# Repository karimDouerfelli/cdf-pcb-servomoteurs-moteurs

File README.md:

# 🛠️ PCB Servomoteurs & Moteurs – Coupe de France de Robotique 2026

Ce projet est un PCB dédié au pilotage de **moteurs** et **servomoteurs**, conçu pour la **Coupe de France de Robotique 2026**.

## ⚙️ Fonctionnalités principales

- Contrôle de servomoteurs via :
  - **UART**
  - **PWM**
- Carte en **4 couches** avec une **couche Power** divisée en 3 zones.

---

## 🧩 Schéma

### Schéma global :

### STM32 et ses compléments :

### Régulateurs :

---

## 🧱 Empreintes

---

## 🧵 Routage

### Placement des composants :

---

## 🧭 Couches PCB

- **GND Layer** :  

- **Top Layer (Rouge)** :  

- **Bottom Layer (Bleue)** :  

- **Power Layer** :  

---

## 📏 Dimensionnement des pistes

Nous avons utilisé la formule suivante pour calculer la largeur des pistes selon le courant attendu :

---

## 🙏 Remerciements

Merci à **@CaptainJaja** pour son aide sur le projet ❤️  

---

## 💬 Retours bienvenus

N'hésitez pas à **ouvrir une issue** ou **créer une pull request** si vous avez des remarques ou des suggestions.

---

---

# 🛠️ PCB for Servomotors & Motors – French Robotics Cup 2026

This project is a PCB designed to control **motors** and especially **servomotors**, built for the **French Robotics Cup 2026**.

## ⚙️ Key Features

- Supports two control modes for servos:
  - **UART**
  - **PWM**
- Built on a **4-layer board** with a **Power layer** split into 3 zones.

---

## 🧩 Schematics

### Global schematic:

### STM32 and peripherals:

### Voltage regulators:

---

## 🧱 Footprints

---

## 🧵 Routing

### Component placement:

---

## 🧭 PCB Layers

- **GND Layer**  

- **Top Layer (Red)**  

- **Bottom Layer (Blue)**  

- **Power Layer**  

---

## 📏 Trace Sizing

Trace widths were calculated using the following formula based on expected current:

---

## 🙏 Acknowledgments

Big thanks to **@CaptainJaja** for contributions ❤️  

---

## 💬 Feedback

Feel free to **open an issue** or **submit a pull request** if you have ideas or improvements to suggest.

---

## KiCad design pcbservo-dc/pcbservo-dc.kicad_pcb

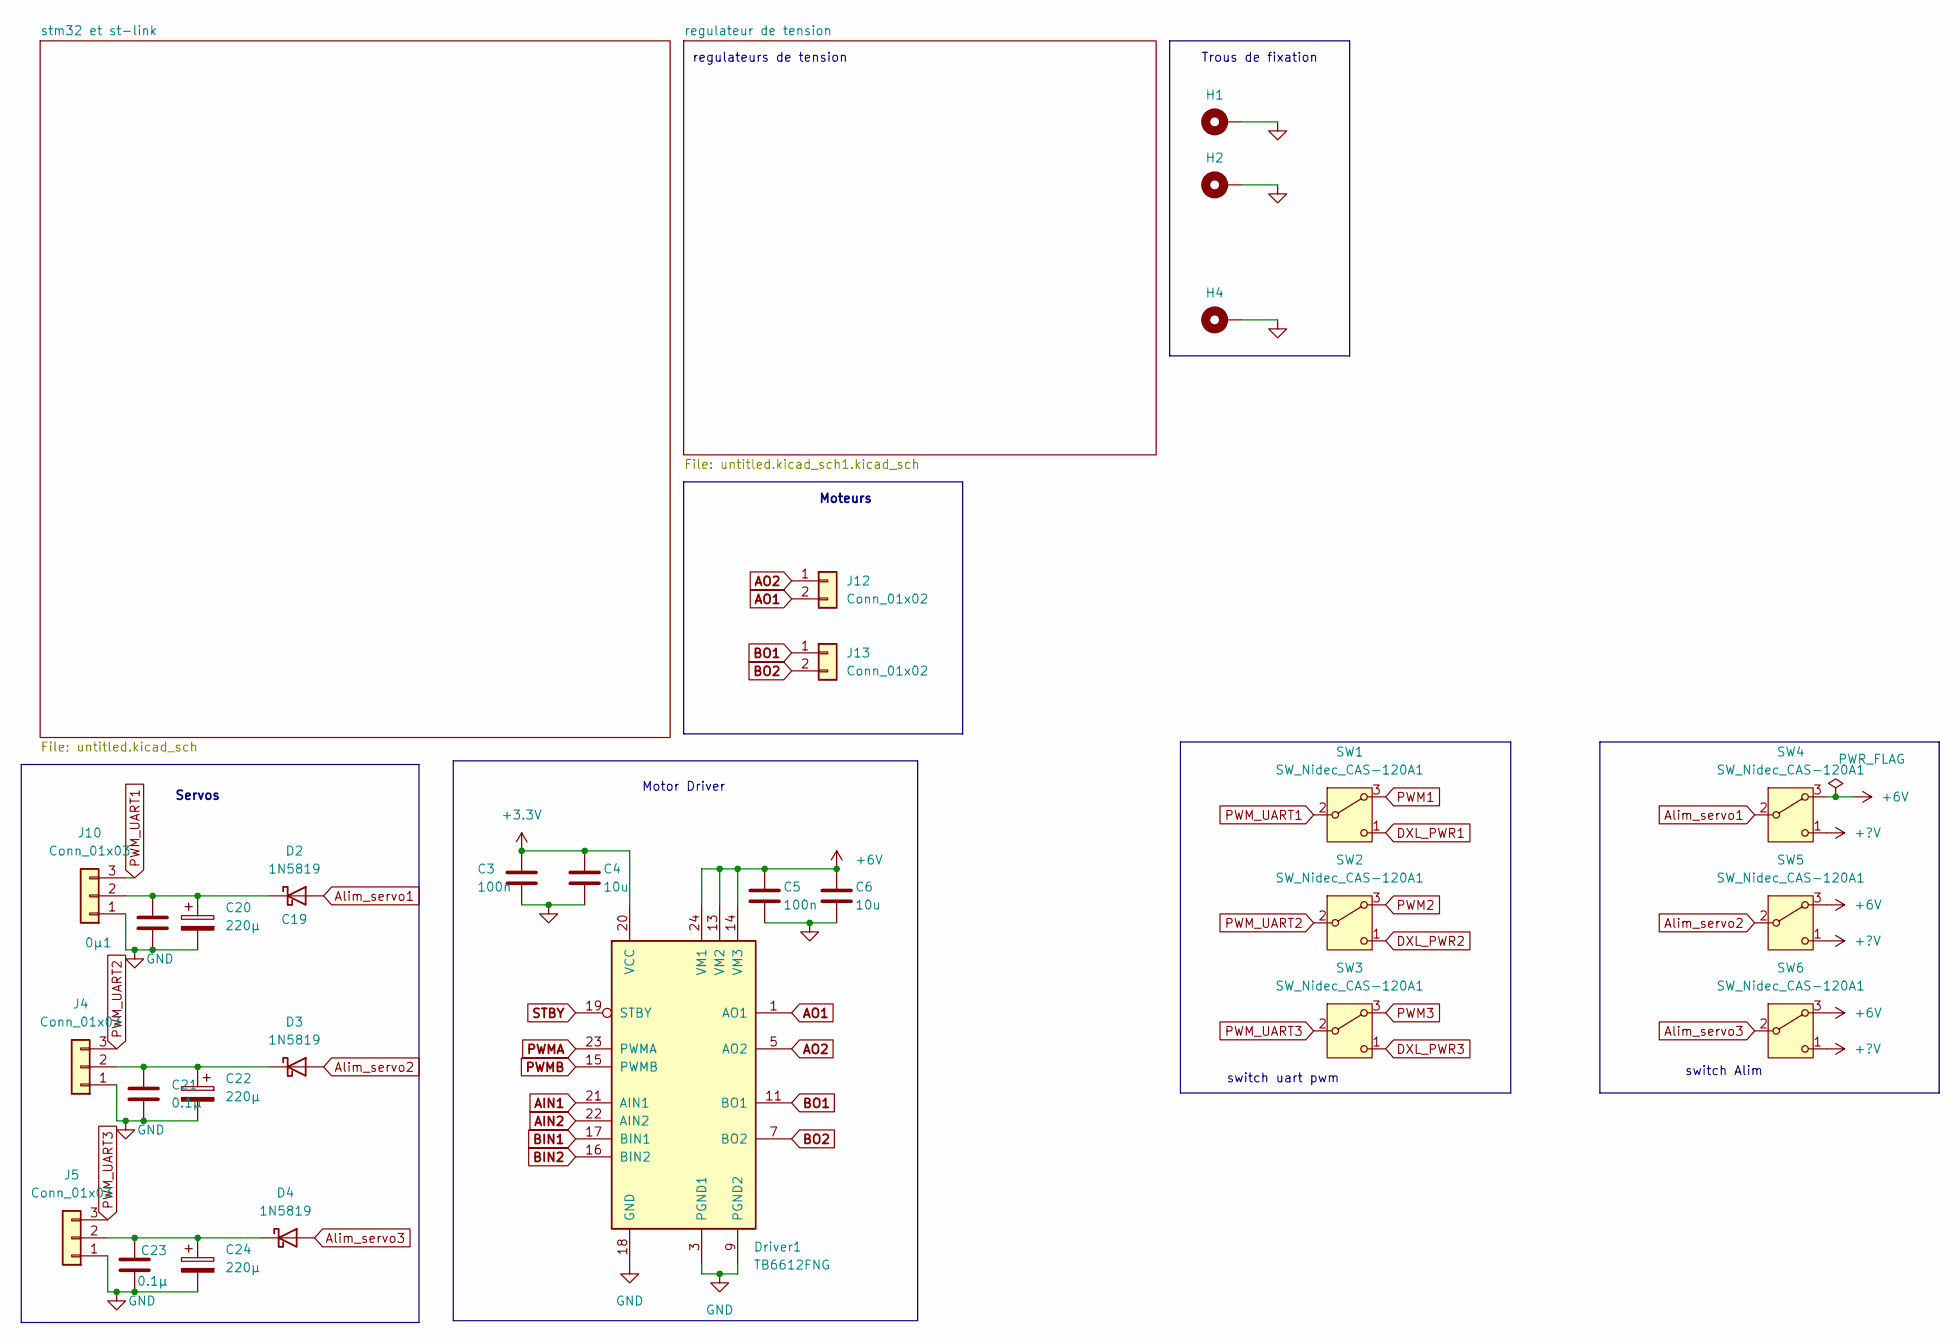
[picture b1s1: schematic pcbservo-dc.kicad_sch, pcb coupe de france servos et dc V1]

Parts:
C3, C5: 100n; C_0402_1005Metric
C4, C6: 10u; C_0805_2012Metric
C19: 0µ1; C_0805_2012Metric
C20, C22, C24: 220µ; CAPPRD500W60D1000H2500
C21, C23: 0.1µ; C_0805_2012Metric
D2, D3, D4: 1N5819; D_SOD-123
Driver1: TB6612FNG; SSOP-24_5.3x8.2mm_P0.65mm
H1, H2, H4: MountingHole_Pad; MountingHole_2.7mm_M2.5_Pad
J4, J5, J10: Conn_01x03; JST_EH_B3B-EH-A_1x03_P2.50mm_Vertical
J12, J13: Conn_01x02; JST_EH_B2B-EH-A_1x02_P2.50mm_Vertical
SW1, SW2, SW3, SW4, SW5, SW6: SW_Nidec_CAS-120A1; Nidec_Copal_CAS-120A

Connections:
+3.3V: C3.1, C4.1, Driver1.20 (VCC); also elsewhere on the board
+6V: C5.1, C6.1, Driver1.13 (VM2), Driver1.14 (VM3), Driver1.24 (VM1), SW4.3 (A), SW5.3 (A), SW6.3 (A); also elsewhere on the board
+?V: SW4.1 (C), SW5.1 (C), SW6.1 (C); also elsewhere on the board
AIN1: Driver1.21 (AIN1); also elsewhere on the board
AIN2: Driver1.22 (AIN2); also elsewhere on the board
AO1: Driver1.1 (AO1), Driver1.2 (AO1), J12.2
AO2: Driver1.5 (AO2), Driver1.6 (AO2), J12.1
Alim_servo1: D2.2 (A), SW4.2 (B)
Alim_servo2: D3.2 (A), SW5.2 (B)
Alim_servo3: D4.2 (A), SW6.2 (B)
BIN1: Driver1.17 (BIN1); also elsewhere on the board
BIN2: Driver1.16 (BIN2); also elsewhere on the board
BO1: Driver1.11 (BO1), Driver1.12 (BO1), J13.1
BO2: Driver1.7 (BO2), Driver1.8 (BO2), J13.2
DXL_PWR1: SW1.1 (C); also elsewhere on the board
DXL_PWR2: SW2.1 (C); also elsewhere on the board
DXL_PWR3: SW3.1 (C); also elsewhere on the board
GND: C3.2, C4.2, C5.2, C6.2, C19.2, C20.2, C21.2, C22.2, C23.2, C24.2, Driver1.3 (PGND1), Driver1.4 (PGND1), Driver1.9 (PGND2), Driver1.10 (PGND2), Driver1.18 (GND), H1.1, H2.1, H4.1, J4.1, J5.1, J10.1; also elsewhere on the board
unnamed: C19.1, C20.1, D2.1 (K), J10.2
unnamed: C21.1, C22.1, D3.1 (K), J4.2
unnamed: C23.1, C24.1, D4.1 (K), J5.2
PWM1: SW1.3 (A); also elsewhere on the board
PWM2: SW2.3 (A); also elsewhere on the board
PWM3: SW3.3 (A); also elsewhere on the board
PWMA: Driver1.23 (PWMA); also elsewhere on the board
PWMB: Driver1.15 (PWMB); also elsewhere on the board
PWM_UART1: J10.3, SW1.2 (B)
PWM_UART2: J4.3, SW2.2 (B)
PWM_UART3: J5.3, SW3.2 (B)
STBY: Driver1.19 (STBY); also elsewhere on the board

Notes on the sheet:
Trous de fixation
switch uart pwm
Servos
switch Alim
regulateurs de tension
Moteurs
Motor Driver

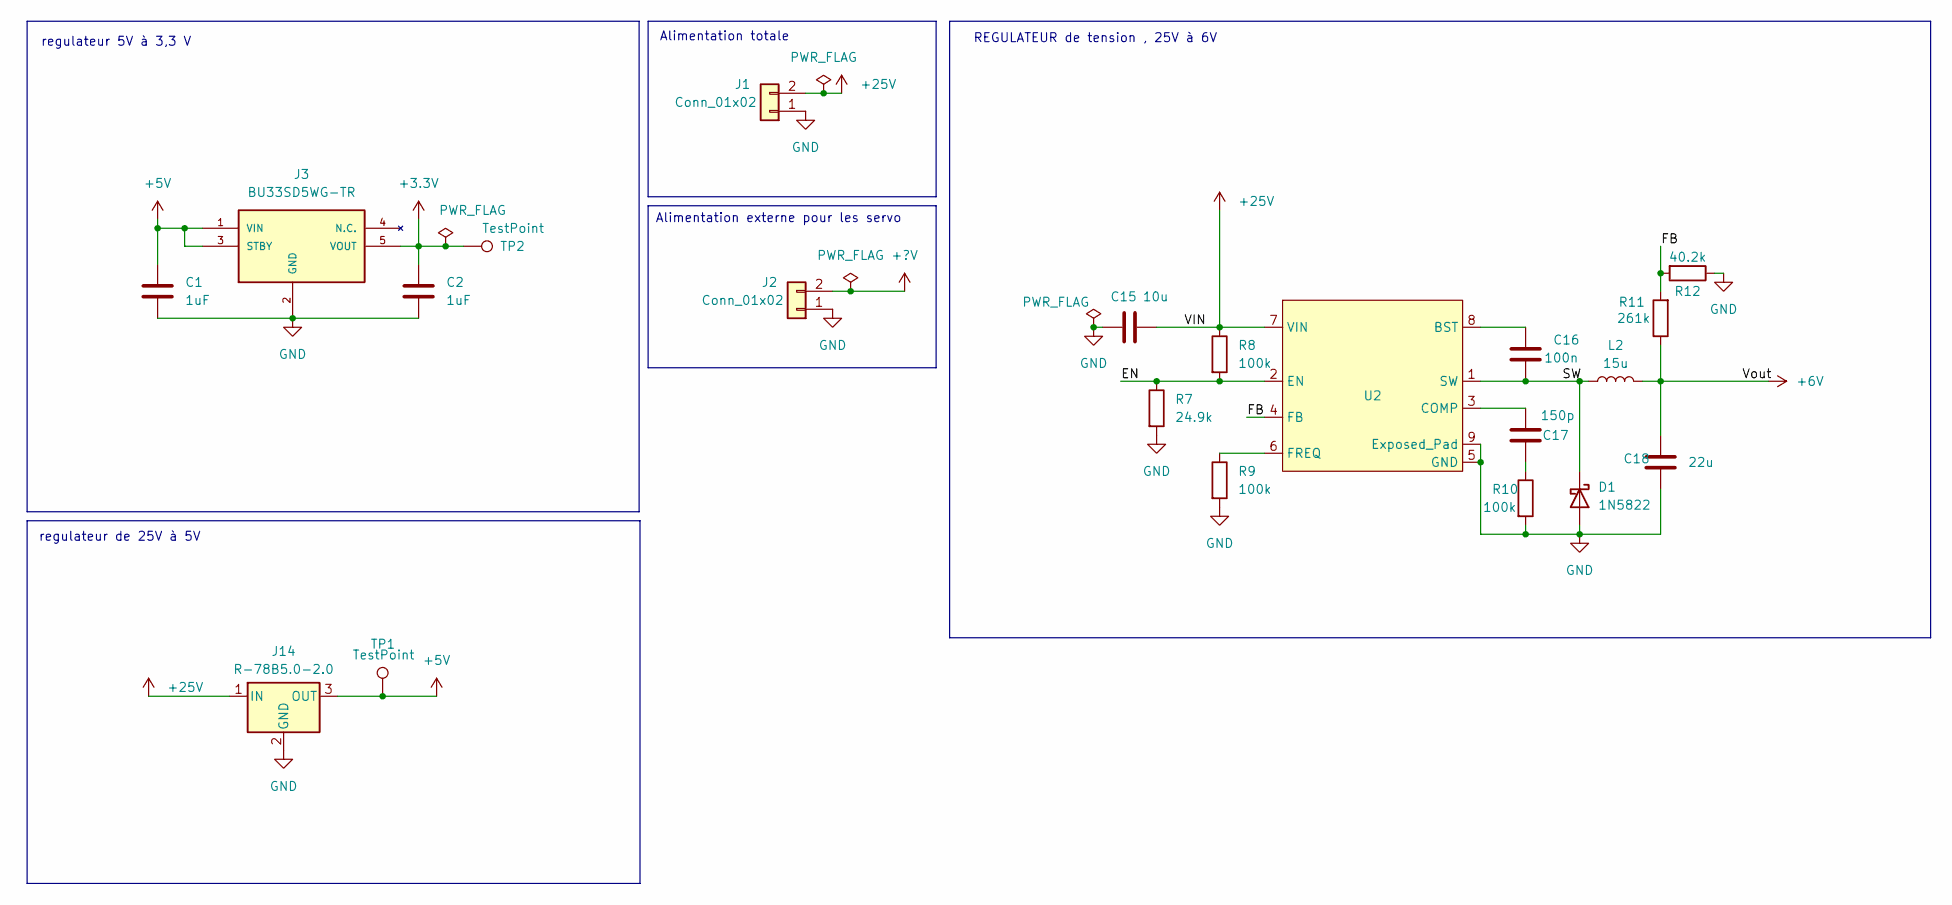
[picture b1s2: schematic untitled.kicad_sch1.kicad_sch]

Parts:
C1, C2: 1uF; C_0603_1608Metric_Pad1.08x0.95mm_HandSolder
C15: 10u; C_0603_1608Metric
C16: 100n; C_0603_1608Metric
C17: 150p; C_0603_1608Metric
C18: 22u; C_0805_2012Metric
D1: 1N5822; D_SMB
J1, J2: Conn_01x02; JST_EH_B2B-EH-A_1x02_P2.50mm_Vertical
J3: BU33SD5WG-TR; SOT-23-5; Mouser_Part_Number 755-BU33SD5WG-TR
J14: R-78B5.0-2.0; Converter_DCDC_RECOM_R-78B-2.0_THT
L2: 15u; L_12x12mm_H4.5mm
R7: 24.9k; R_0603_1608Metric
R8, R9, R10: 100k; R_0603_1608Metric
R11: 261k; R_0603_1608Metric
R12: 40.2k; R_0603_1608Metric
TP1, TP2: TestPoint; TestPoint_Pad_D1.0mm
U2: MP1584-SOICP8

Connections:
+3.3V: C2.1, J3.5 (VOUT), TP2.1; also elsewhere on the board
+5V: C1.1, J3.1 (VIN), J3.3 (STBY), J14.3 (OUT), TP1.1; also elsewhere on the board
+6V: C18.1, L2.2, R11.1; also elsewhere on the board
+25V: C15.1, J1.2, J14.1 (IN), R8.1, U2.7 (VIN)
+?V: J2.2; also elsewhere on the board
/regulateur de tension/EN: R7.1, R8.2, U2.2 (EN)
/regulateur de tension/FB: R11.2, R12.2, U2.4 (FB)
/regulateur de tension/SW: C16.2, D1.1 (K), L2.1, U2.1 (SW)
GND: C1.2, C2.2, C15.2, C18.2, D1.2 (A), J1.1, J2.1, J3.2 (GND), J14.2 (GND), R7.2, R9.2, R10.2, R12.1, U2.5 (GND), U2.9 (Exposed_Pad); also elsewhere on the board
unnamed: C17.2, R10.1
unnamed: C16.1, U2.8 (BST)
unnamed: C17.1, U2.3 (COMP)
unnamed: R9.1, U2.6 (FREQ)

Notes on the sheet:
regulateur 5V à 3,3 V
Alimentation externe pour les servo
REGULATEUR de tension , 25V à 6V
regulateur de 25V à 5V
Alimentation totale

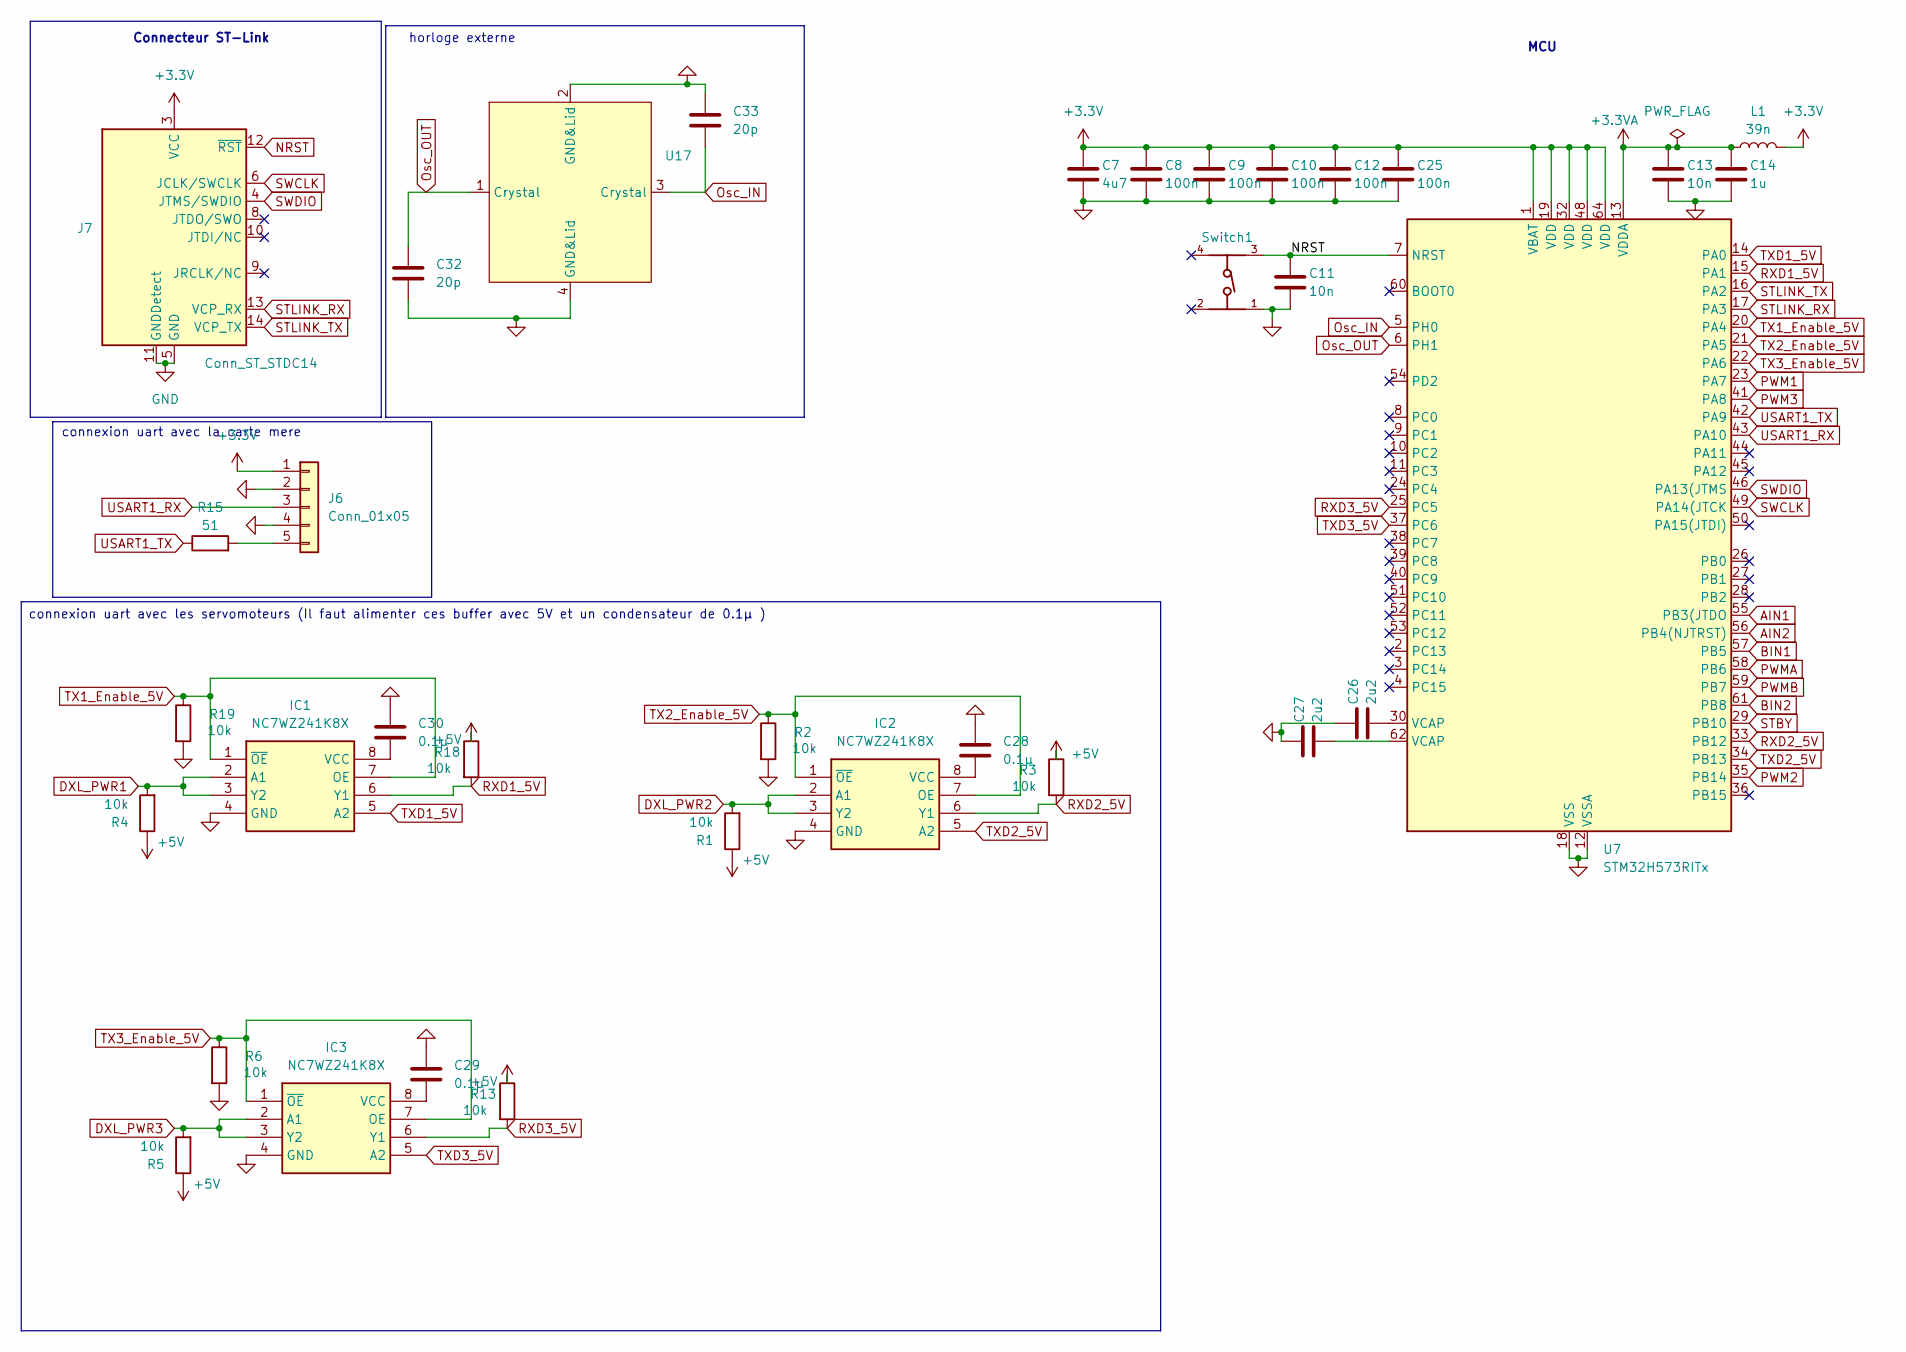
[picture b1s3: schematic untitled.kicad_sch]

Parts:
C7: 4u7; C_0805_2012Metric
C8, C9, C10, C12, C25: 100n; C_0402_1005Metric
C11, C13: 10n; C_0402_1005Metric
C14: 1u; C_0402_1005Metric
C26, C27: 2u2; C_0805_2012Metric
C28, C29, C30: 0.1µ; C_0603_1608Metric
C32, C33: 20p; C_0603_1608Metric
IC1, IC2, IC3: NC7WZ241K8X; UQFN8 1.6X1.6, 0.5P; Mouser Part Number 512-NC7WZ241K8X
J6: Conn_01x05; JST_EH_B5B-EH-A_1x05_P2.50mm_Vertical
J7: Conn_ST_STDC14; PinHeader_2x07_P1.27mm_Vertical_SMD
L1: 39n; L_0603_1608Metric
R1, R2, R3, R4, R5, R6, R13, R18, R19: 10k; R_0402_1005Metric
R15: 51; R_0402_1005Metric
Switch1: 430471025826; BOUTONPOUSSOIR; PART-NUMBER 430471025826
U7: STM32H573RITx; LQFP-64_10x10mm_P0.5mm
U17: Crystal_SMD_3225-4Pin_3.2x2.5mm

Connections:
+3.3V: C7.1, C8.1, C9.1, C10.1, C12.1, C25.1, J6.1, J7.3 (VCC), L1.2, U7.1 (VBAT), U7.19 (VDD), U7.32 (VDD), U7.48 (VDD), U7.64 (VDD); also elsewhere on the board
+3.3VA: C13.1, C14.1, L1.1, U7.13 (VDDA)
+5V: R1.1, R3.1, R4.1, R5.1, R13.1, R18.1; also elsewhere on the board
AIN1: U7.55 (PB3(JTDO); also elsewhere on the board
AIN2: U7.56 (PB4(NJTRST)); also elsewhere on the board
BIN1: U7.57 (PB5); also elsewhere on the board
BIN2: U7.61 (PB8); also elsewhere on the board
DXL_PWR1: IC1.2 (A1), IC1.3 (Y2), R4.2; also elsewhere on the board
DXL_PWR2: IC2.2 (A1), IC2.3 (Y2), R1.2; also elsewhere on the board
DXL_PWR3: IC3.2 (A1), IC3.3 (Y2), R5.2; also elsewhere on the board
GND: C7.2, C8.2, C9.2, C10.2, C11.2, C12.2, C13.2, C14.2, C25.2, C26.1, C27.1, C28.1, C29.1, C30.1, C32.2, C33.1, IC1.4 (GND), IC2.4 (GND), IC3.4 (GND), J6.2, J6.4, J7.5 (GND), J7.7 (GND), J7.11 (GNDDetect), R2.2, R6.2, R19.2, Switch1.1, U7.12 (VSSA), U7.18 (VSS), U7.31 (VSS), U7.47 (VSS), U7.63 (VSS), U17.2 (GND&Lid), U17.4 (GND&Lid); also elsewhere on the board
NRST: C11.1, J7.12 (~RST), Switch1.3, U7.7 (NRST)
unnamed: C26.2, U7.30 (VCAP)
unnamed: C27.2, U7.62 (VCAP)
unnamed: C30.2, IC1.8 (VCC)
unnamed: C28.2, IC2.8 (VCC)
unnamed: C29.2, IC3.8 (VCC)
unnamed: J6.5, R15.2
Osc_IN: C33.2, U7.5 (PH0), U17.3 (Crystal)
Osc_OUT: C32.1, U7.6 (PH1), U17.1 (Crystal)
PWM1: U7.23 (PA7); also elsewhere on the board
PWM2: U7.35 (PB14); also elsewhere on the board
PWM3: U7.41 (PA8); also elsewhere on the board
PWMA: U7.58 (PB6); also elsewhere on the board
PWMB: U7.59 (PB7); also elsewhere on the board
RXD1_5V: IC1.6 (Y1), R18.2, U7.15 (PA1)
RXD2_5V: IC2.6 (Y1), R3.2, U7.33 (PB12)
RXD3_5V: IC3.6 (Y1), R13.2, U7.25 (PC5)
STBY: U7.29 (PB10); also elsewhere on the board
STLINK_RX: J7.13 (VCP_RX), U7.17 (PA3)
STLINK_TX: J7.14 (VCP_TX), U7.16 (PA2)
SWCLK: J7.6 (JCLK/SWCLK), U7.49 (PA14(JTCK)
SWDIO: J7.4 (JTMS/SWDIO), U7.46 (PA13(JTMS)
TX1_Enable_5V: IC1.1 (~OE), IC1.7 (OE), R19.1, U7.20 (PA4)
TX2_Enable_5V: IC2.1 (~OE), IC2.7 (OE), R2.1, U7.21 (PA5)
TX3_Enable_5V: IC3.1 (~OE), IC3.7 (OE), R6.1, U7.22 (PA6)
TXD1_5V: IC1.5 (A2), U7.14 (PA0)
TXD2_5V: IC2.5 (A2), U7.34 (PB13)
TXD3_5V: IC3.5 (A2), U7.37 (PC6)
USART1_RX: J6.3, U7.43 (PA10)
USART1_TX: R15.1, U7.42 (PA9)

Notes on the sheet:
connexion uart avec la carte mere
horloge externe
Connecteur ST-Link
MCU
connexion uart avec les servomoteurs (Il faut alimenter ces buffer avec 5V et un condensateur de 0.1µ )

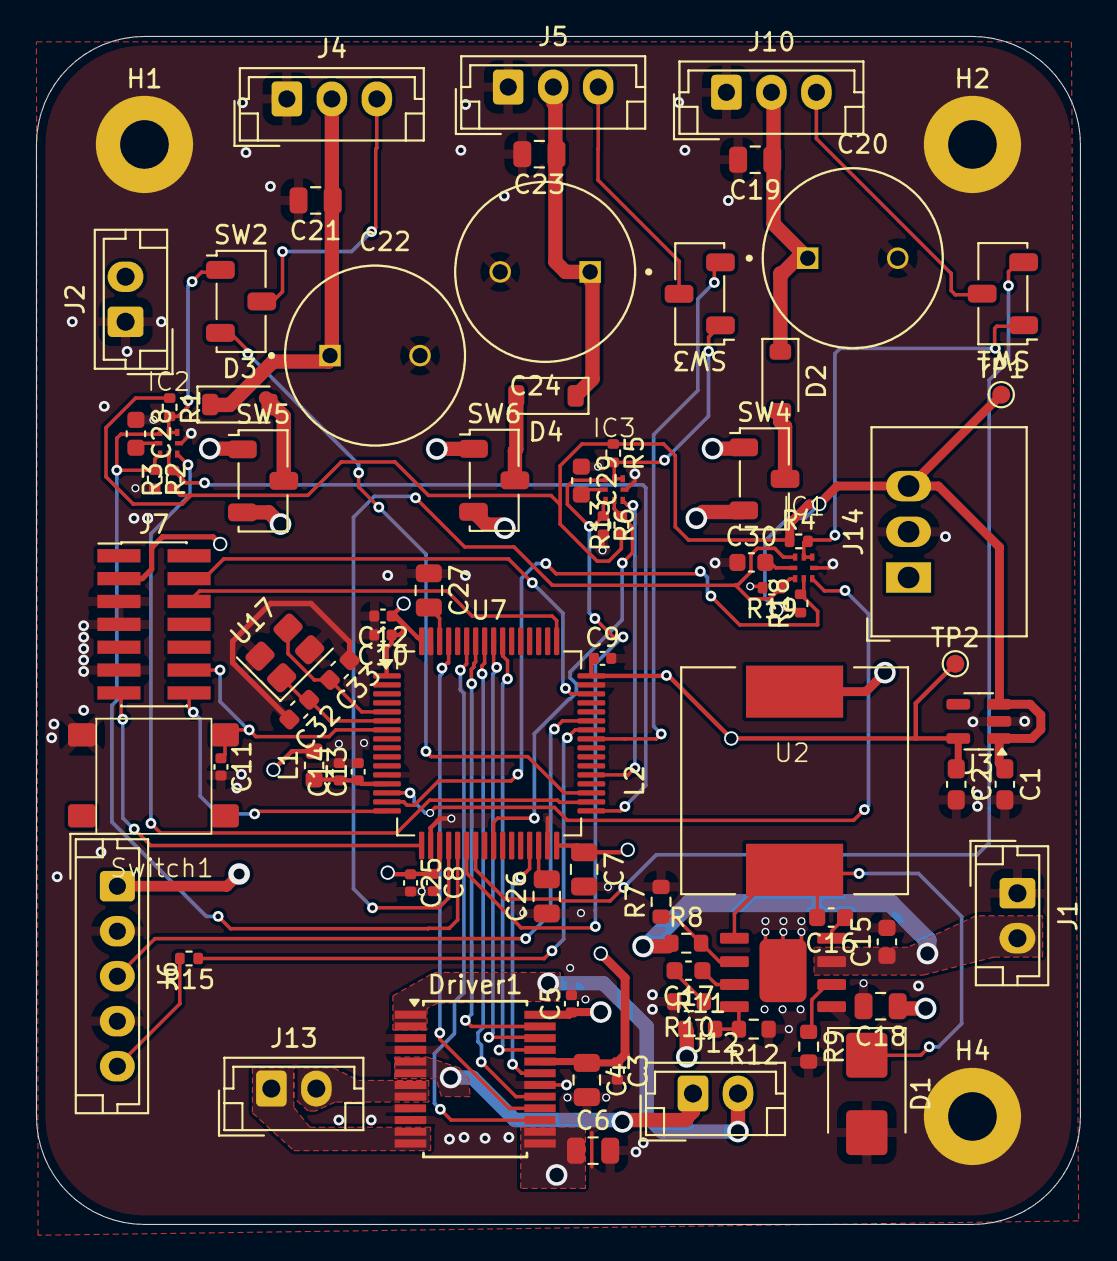
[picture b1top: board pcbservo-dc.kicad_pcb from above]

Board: 4 copper layers, 58.0 x 66.0 mm, 84 parts (0 on the bottom side), 64 nets.

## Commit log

2025-09-11 uart a jour
2025-09-11 modification des condensateur et des diode
2025-09-16 changement de quelques empreinte
